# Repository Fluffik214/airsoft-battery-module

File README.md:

# Airsoft Battery Module

This is a USB-C PD charger and cell monitor for a **3S LiPo** that lives in an airsoft stock tube. It has one USB-C port. A PD charger charges the pack through it, and a phone plugged into the same port shows each cell's voltage and charge % in the companion Android app.

| | |
|---|---|
| Board | 135 × 21 mm, 2 layers, SMT only, no BGA |
| Pack | 3S LiPo (made for an iPower 1450 mAh stick). **Connects through the JST-XH balance plug only** (charging and cell sensing); the Deans lead goes straight to the gun |
| Charging | USB-C PD at 15 V (CH224K) → BQ25798 buck-boost charger |
| Monitoring | BQ7692003 (per-cell voltage, NTC, balancing) → STM32F042 → USB CDC |
| Idle drain | about 1 µA when unplugged |

## How it works

- **One port, two jobs.** On a PD charger the module charges. On a phone it only reports (5 V never charges, so the phone isn't drained). It never does both at once.
- **Charging rules:**
  - It starts after USB has stayed between 12 and 17 V for 5 s, then charges to your preset: Full, a custom %, Storage (3.80 V/cell) or Off.
  - If USB goes above 17 V, charging is cut immediately.
- **Per-cell control, like a hobby balance charger.** When a cell is full, it is held there and bled while the current is turned down, so the other cells can catch up. No cell goes more than 10 mV over the target.
- **JP2 solder jumper (back of the board).** Open (default) = slow charge, 700 mA. Bridged = fast charge, 1.4 A. Both currents can be changed in the app. Check your balance lead: on thin 26 AWG wires stay on slow charge.
- **Charging through the balance plug.** The charge current runs in the balance lead's outer wires (pins 1 and 4) through a 2.5 A fuse. The firmware pauses the charger for under a second every few seconds to read the cells without the wire voltage drop, so all three cells are measured accurately.
- **Cell LEDs.** Three wire pads (A, B, C) near the USB-C drive one red/green LED per cell on a small 20 × 10 mm LED board (`led_board/`) that sits on top of the stock tube: red = cell still charging, green = cell full. Solder A to A, B to B, C to C.
- **Event log in flash.** Faults (over-voltage, over-temperature, bad cell…) and a report for every charge are stored on the module. The app shows them the next time a phone is connected.

## Repository layout

| Path | Contents |
|---|---|
| `usbc pd airsoft module.kicad_*` | KiCad 10 project: schematic, routed PCB, design rules |
| `schematic.pdf`, `bom.csv` | Schematic printout and bill of materials |
| `DESIGN_NOTES.md` | Hardware notes: power path, pinouts, checks before first power-up |
| `layout_work/` | Python scripts that generated the schematic and placed/routed the PCB |
| `firmware/` | STM32F042 firmware: bare-metal C plus TinyUSB. **`firmware/README.md` is the full guide**, covering protocol, settings, safety rules and how to customize |
| `android/` | Android app: Kotlin, Jetpack Compose, Material 3 |
| `release/` | Prebuilt firmware (`.bin` / `.hex`) and app (`.apk`) |
| `production/` | Gerber zip for the board house, drill files, pick-and-place, BOM, assembly drawings, and `ORDERING.md` (fab settings). `production/led_board/` has the same set for the LED board |
| `led_board/` | KiCad project of the cell-LED board (schematic, routed PCB) plus its generator, checker and routing scripts |
| `3dmodels/` | 3D models KiCad doesn't ship: the J2 balance plug and the cell LED |

## Quick start

1. **Flash the firmware.** A blank chip starts in the USB DFU bootloader. You can also bridge JP1 while plugging in. Then:
   ```
   dfu-util -a 0 -s 0x08000000:leave -D release/airsoft_charger.bin
   ```
   STM32CubeProgrammer works too.
2. **Install the app.** Copy `release/PDCharger-1.0.0.apk` to the phone and install it.
3. **Check the pack.** Plug the module into the phone with a USB-C cable and open the app.
4. **Charge it.** Put the module on a USB-C PD charger that offers 15 V (or 12 V).

### Building from source

- **Firmware:** needs `arm-none-eabi-gcc` (tested with xPack 15.2.1). Run:
  ```
  python firmware/build.py --gcc <path-to-toolchain-bin>
  ```
- **App:** needs JDK 17 and the Android SDK. Run:
  ```
  cd android && ./gradlew assembleRelease
  ```

## Safety

LiPo batteries can catch fire. This is a hobby project with **no warranty**. Check `DESIGN_NOTES.md` before the first power-up. In particular, check your pack's balance plug against `production/assembly/J2-orientation.png`: J2 pin 4 is the pack's negative (black) wire.

## License

© Fluff. Licensed under **[Creative Commons Attribution-NonCommercial-ShareAlike 4.0](LICENSE)** (CC BY-NC-SA 4.0):

- You may copy, build and change this project for **non-commercial** use, if you credit the author and share your changes under the same license.
- **Commercial use, including selling boards, kits or devices built from this design, needs written permission from the author.**

Third-party code in `firmware/lib/` keeps its own license:

- **TinyUSB:** MIT, see `firmware/lib/tinyusb/LICENSE`.
- **ARM CMSIS core headers:** Apache-2.0 (SPDX header in each file).
- **ST device headers:** Apache-2.0, see `firmware/lib/cmsis/LICENSE-ST-cmsis-device-f0.md`.
- **J2 3D model** (`3dmodels/JST_XH_S4B-XH-SM4-TB.step`): from the JLCEDA/EasyEDA Official Library ([lceda.cn](https://lceda.cn/), [easyeda.com](https://easyeda.com)), see `3dmodels/README.md`.

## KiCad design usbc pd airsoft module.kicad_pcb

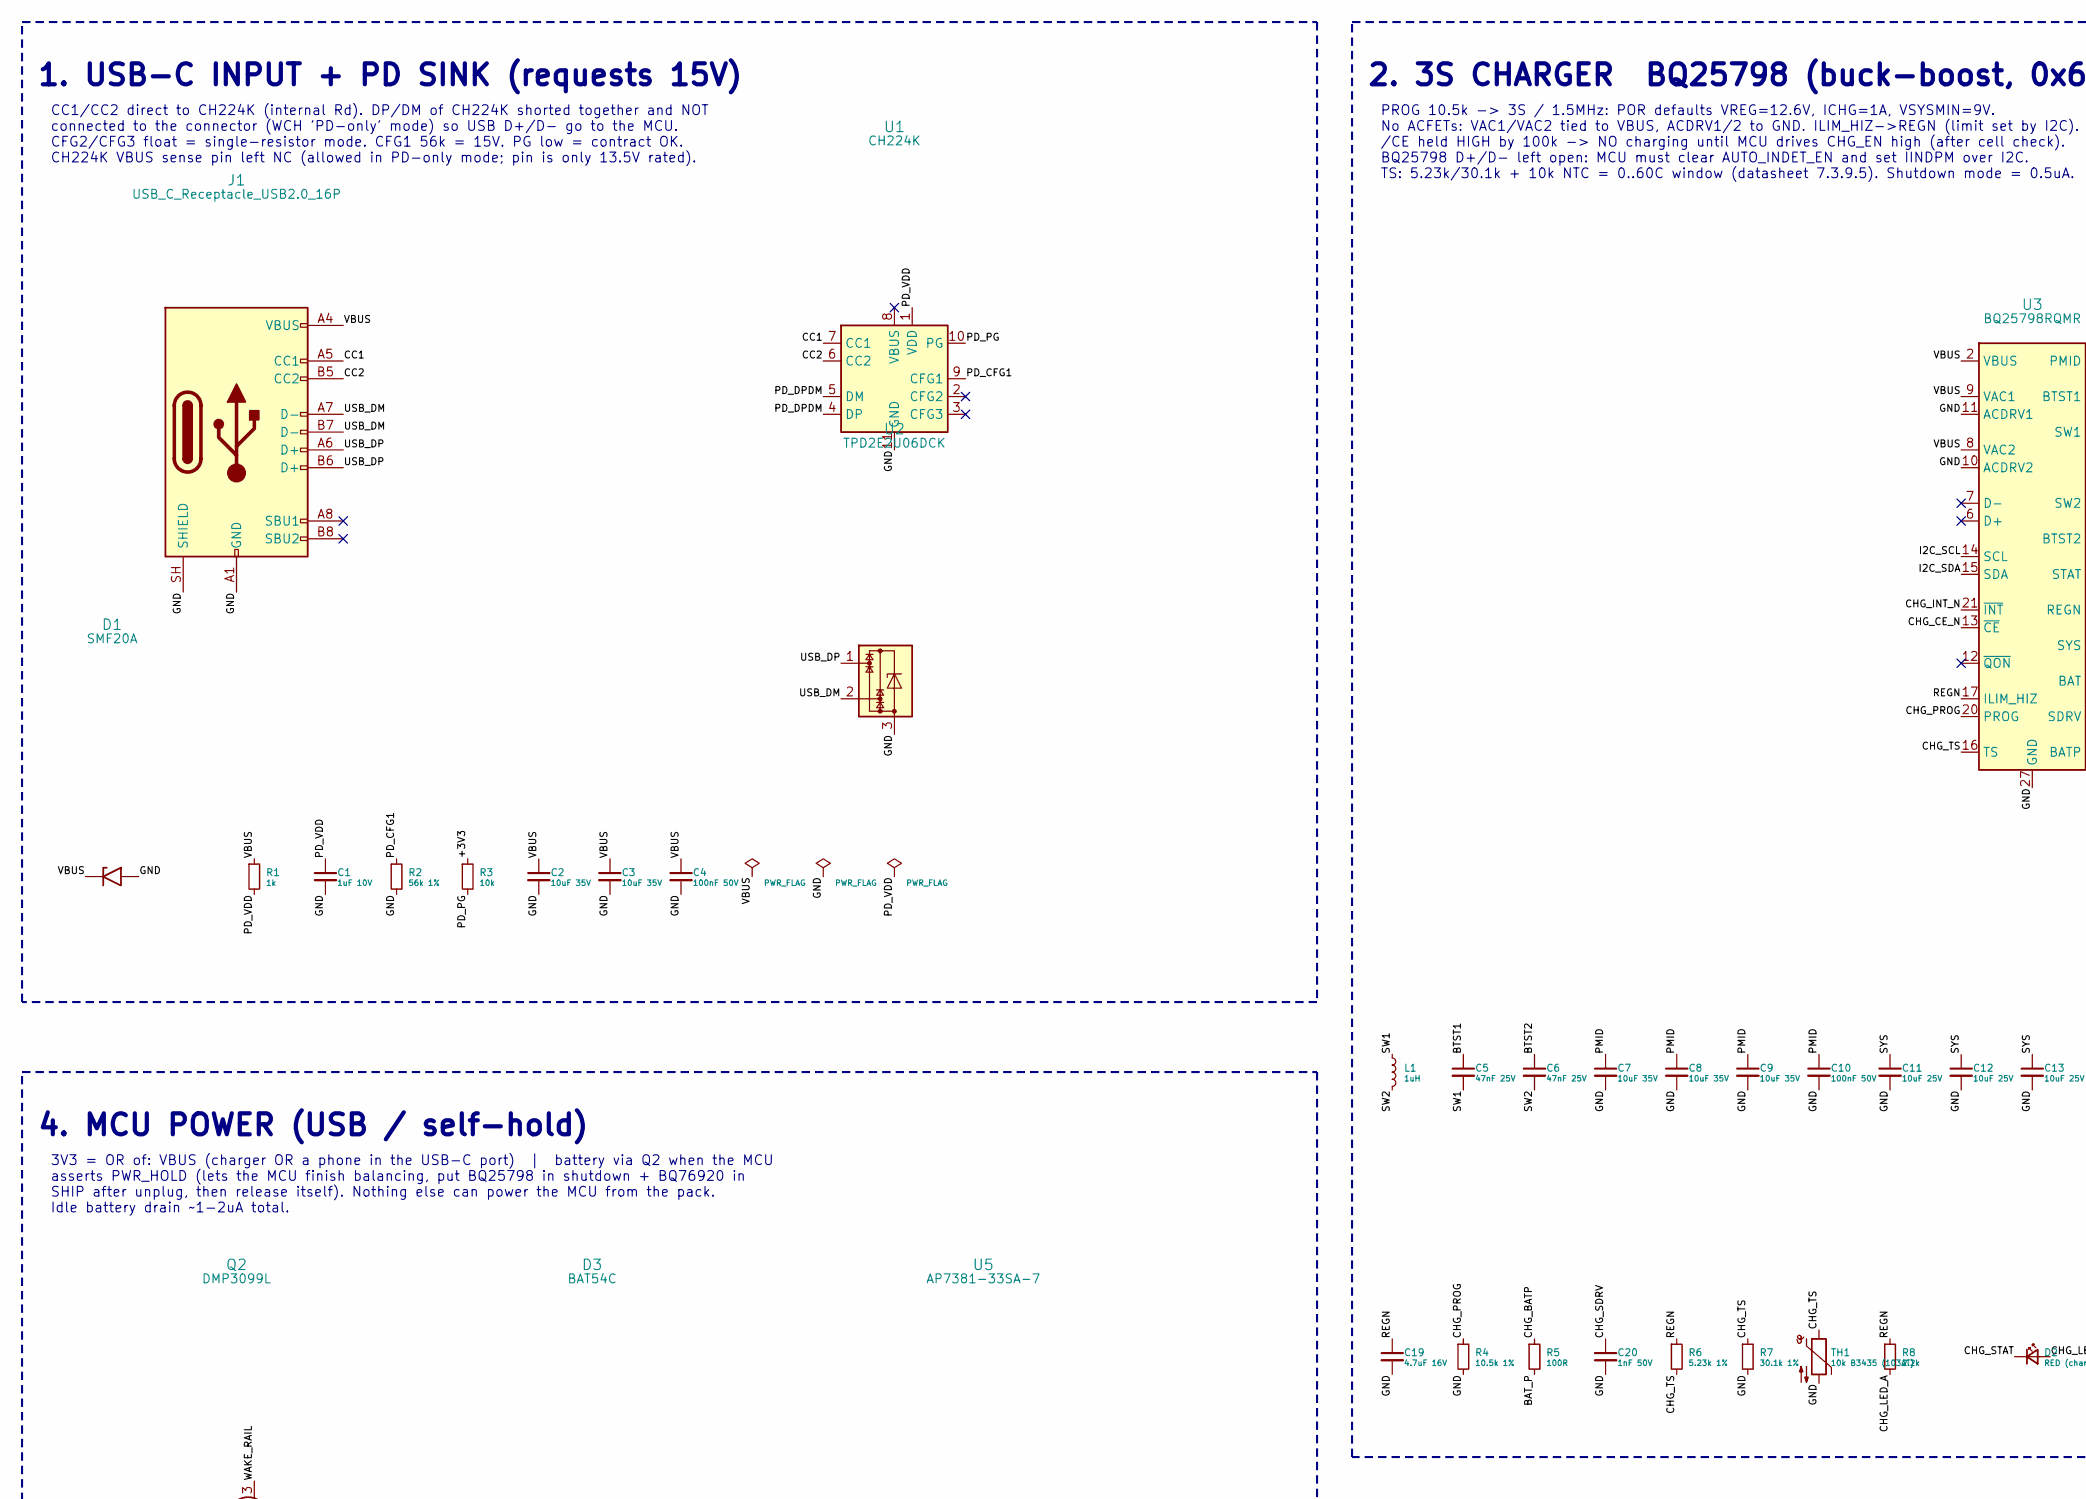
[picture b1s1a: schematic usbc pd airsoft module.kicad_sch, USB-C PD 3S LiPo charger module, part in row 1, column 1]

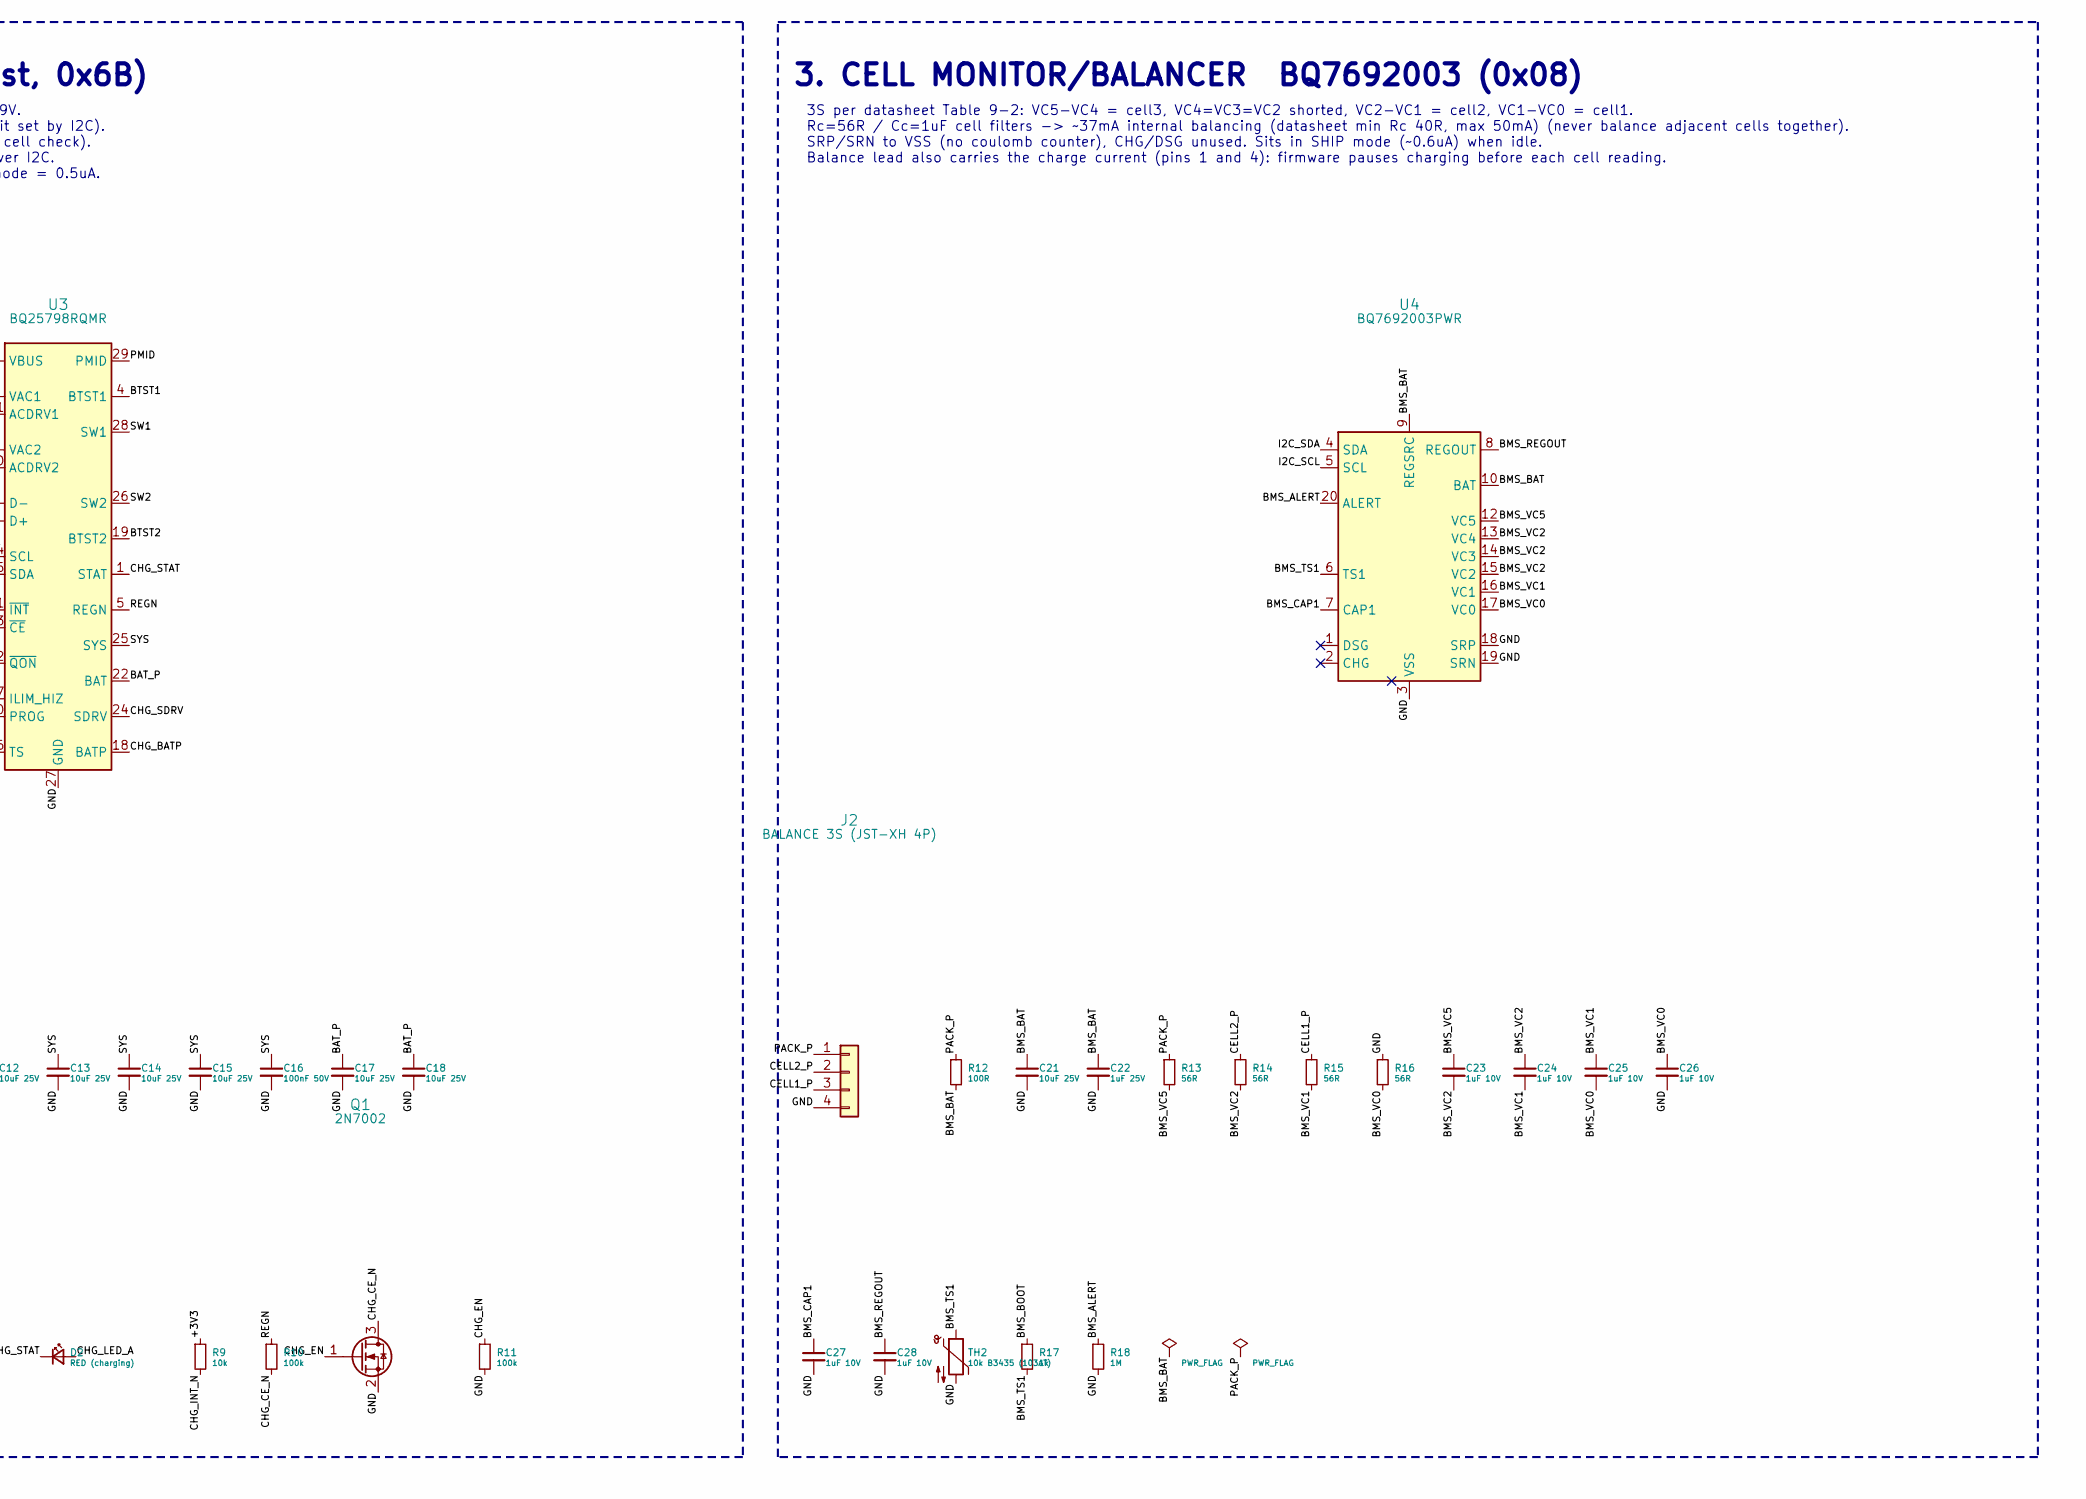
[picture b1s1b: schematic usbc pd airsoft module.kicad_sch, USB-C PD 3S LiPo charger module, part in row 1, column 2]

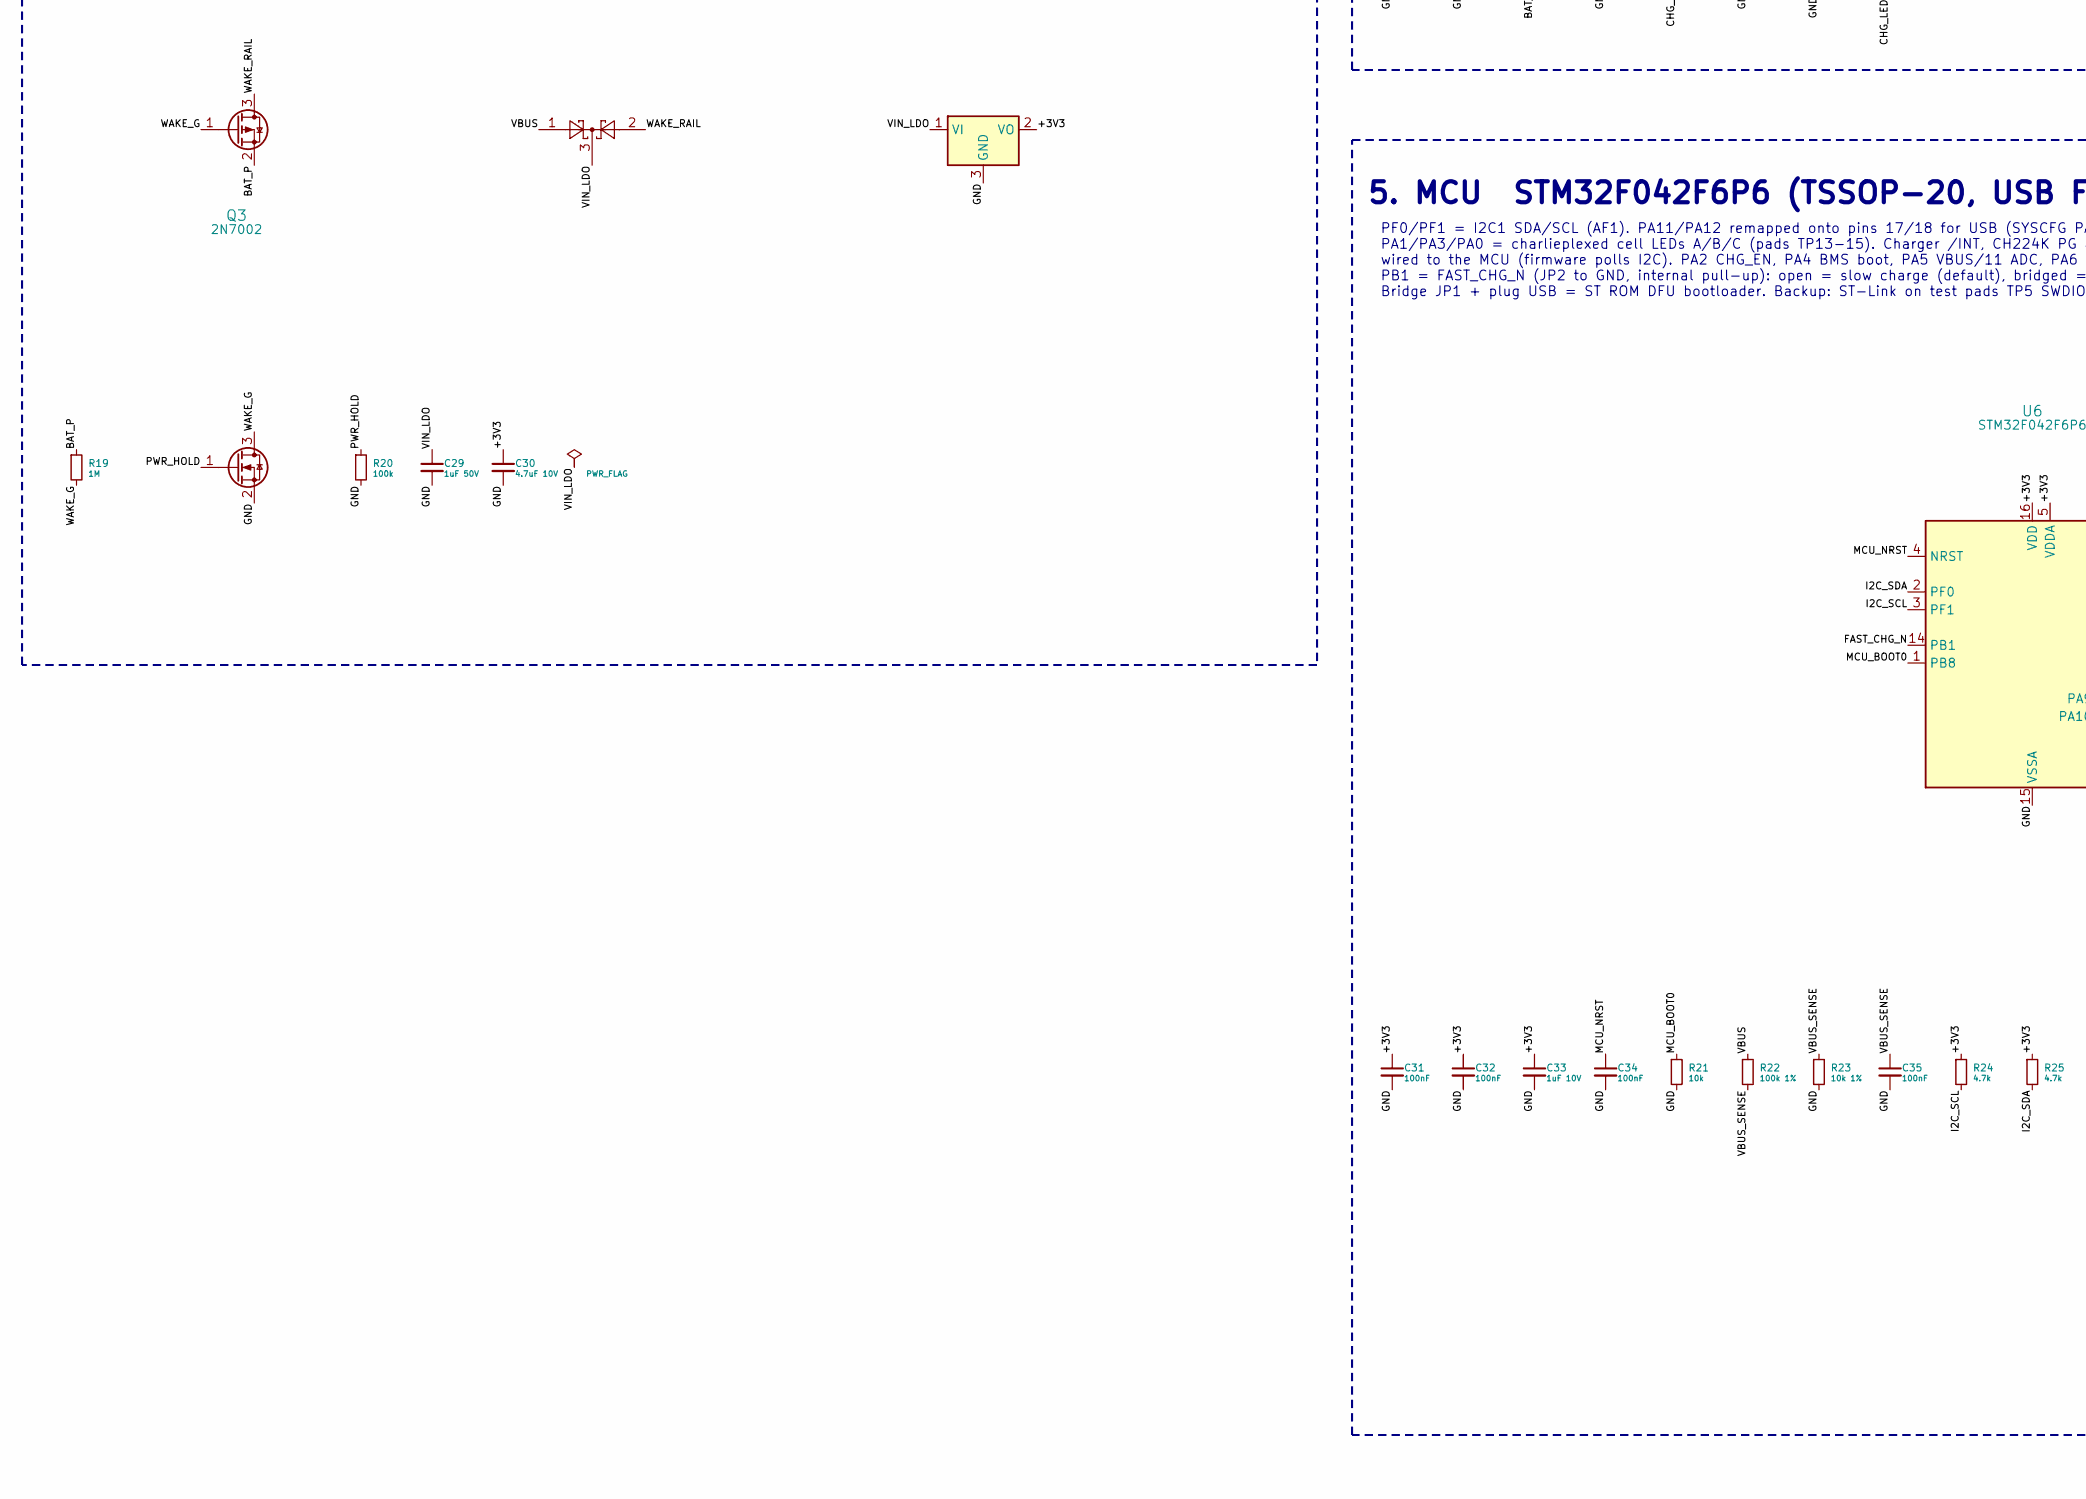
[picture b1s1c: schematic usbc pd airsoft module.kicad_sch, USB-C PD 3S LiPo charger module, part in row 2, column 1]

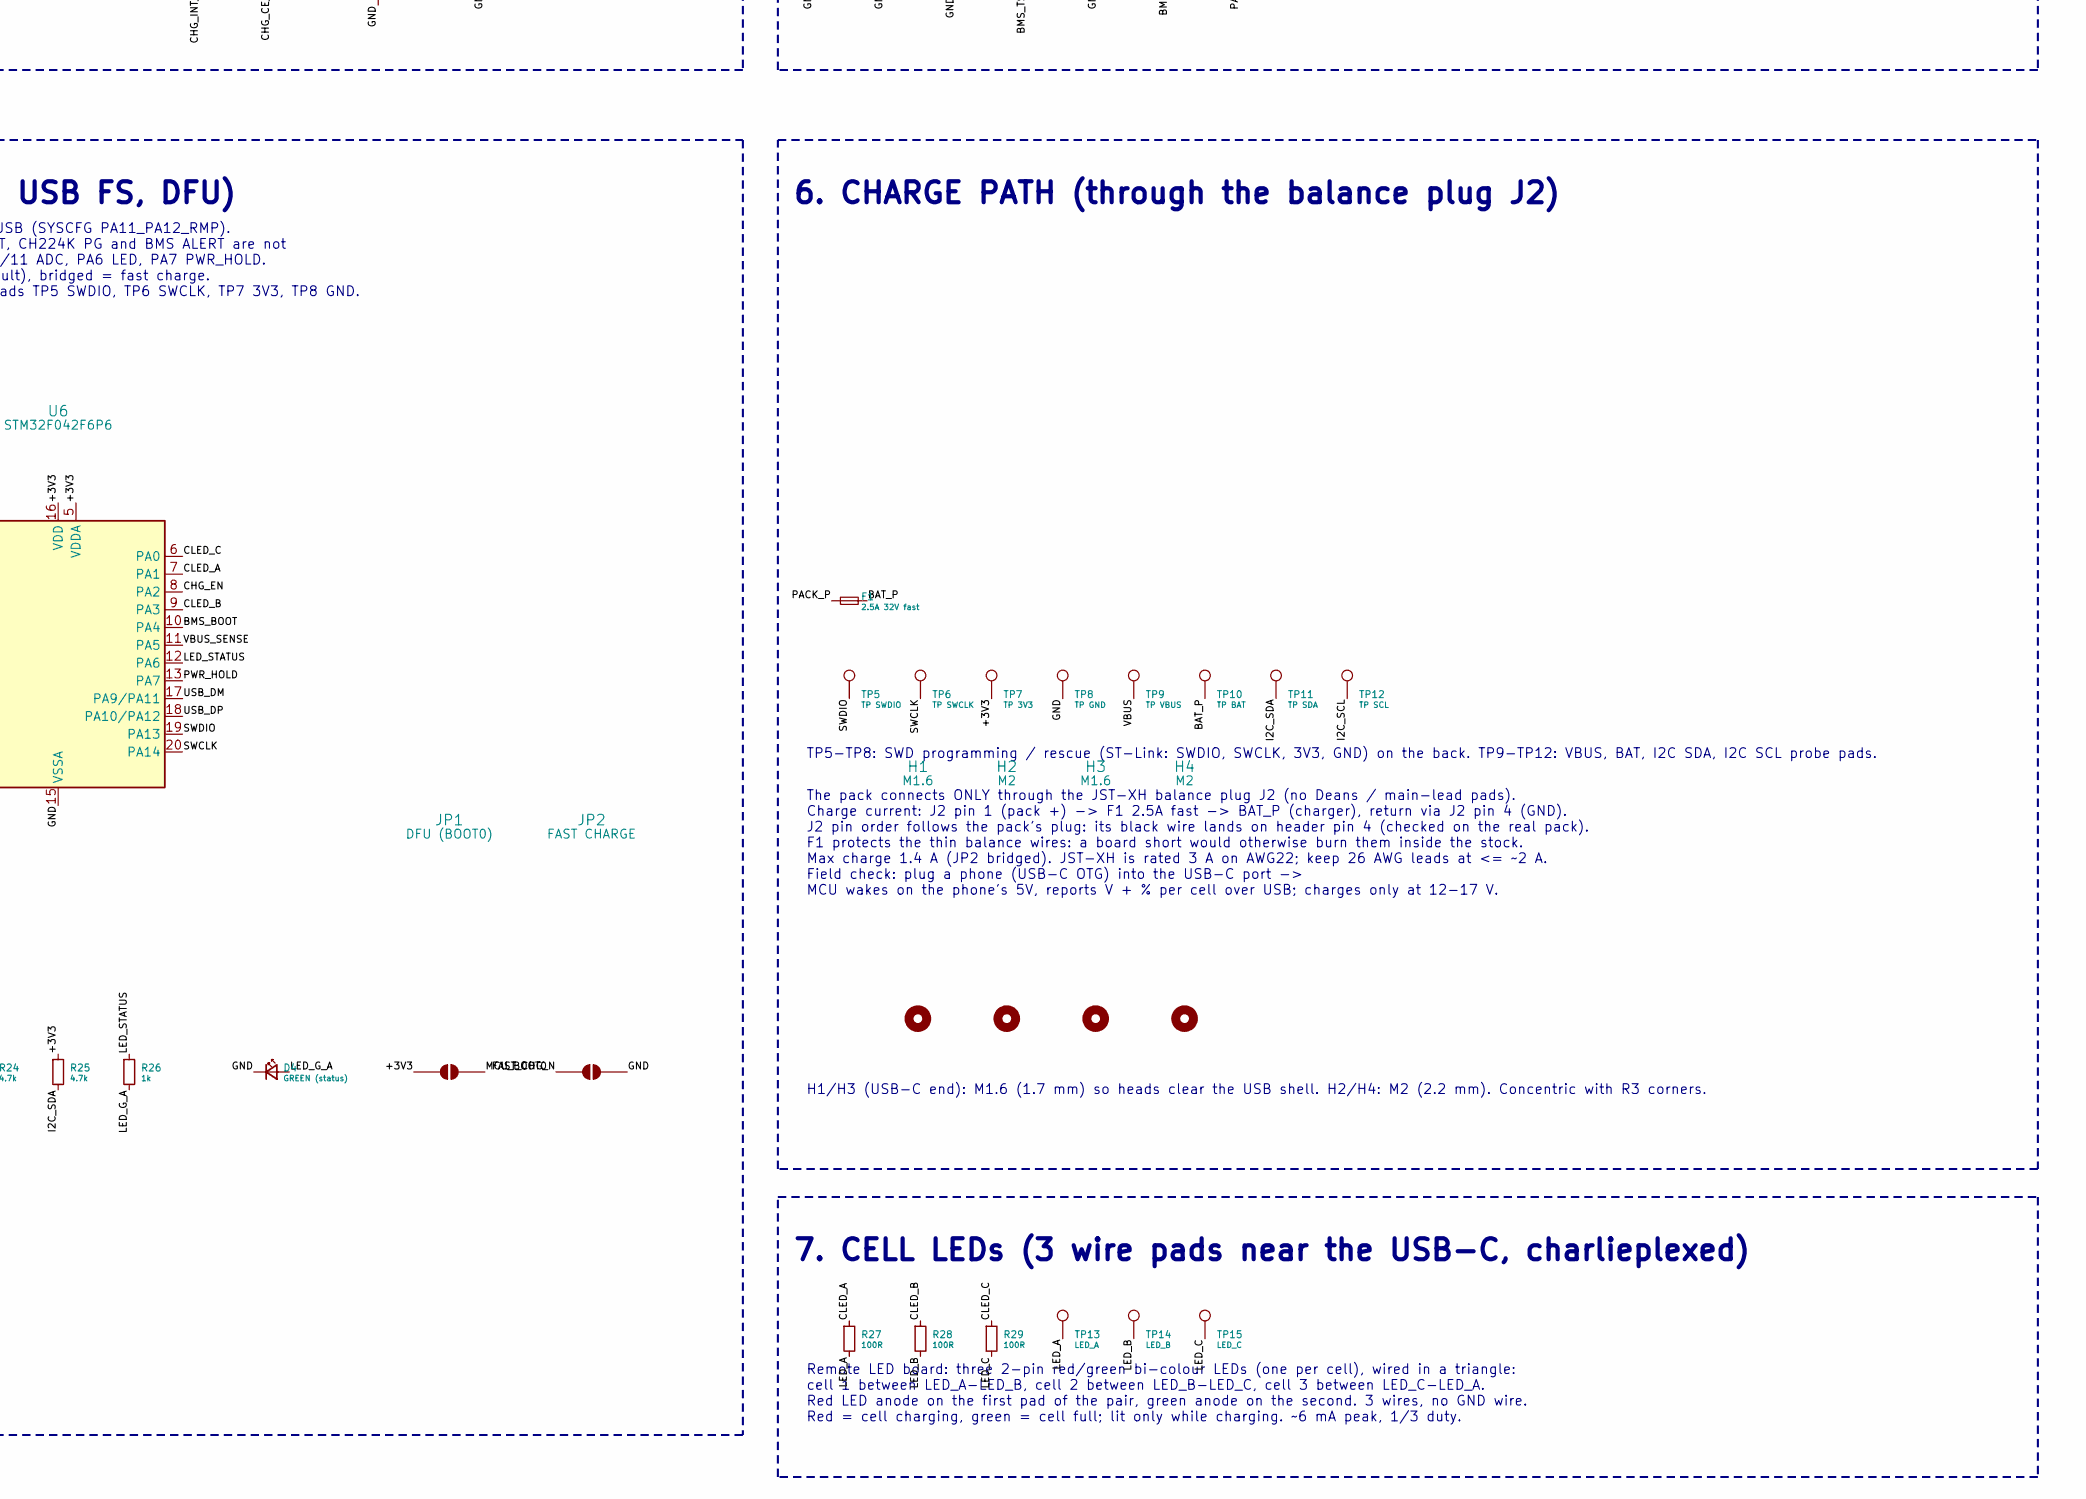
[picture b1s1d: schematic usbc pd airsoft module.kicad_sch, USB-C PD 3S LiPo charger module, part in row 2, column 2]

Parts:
C1, C23, C24, C25, C26, C27, C28, C33: 1uF 10V; C_0402_1005Metric
C2, C3, C7, C8, C9: 10uF 35V; C_0805_2012Metric
C4, C10, C16: 100nF 50V; C_0402_1005Metric
C5, C6: 47nF 25V; C_0402_1005Metric
C11, C12, C13, C14, C15, C17, C18, C21: 10uF 25V; C_0805_2012Metric
C19: 4.7uF 16V; C_0603_1608Metric
C20: 1nF 50V; C_0402_1005Metric
C22: 1uF 25V; C_0603_1608Metric
C29: 1uF 50V; C_0805_2012Metric
C30: 4.7uF 10V; C_0603_1608Metric
C31, C32, C34, C35: 100nF; C_0402_1005Metric
D1: SMF20A; D_SMF; MPN Littelfuse SMF20A (20V TVS)
D2: RED (charging); LED_0603_1608Metric
D3: BAT54C; SOT-23
D4: GREEN (status); LED_0603_1608Metric
F1: 2.5A 32V fast; Fuse_1206_3216Metric; MPN AEM F1206SB2500V032TM (LCSC C310999), 2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
H1, H3: M1.6; MountingHole_1.7mm_M1.6
H2, H4: M2; MountingHole_2.2mm_M2
J1: USB_C_Receptacle_USB2.0_16P; USB_C_Receptacle_HRO_TYPE-C-31-M-12; MPN HRO TYPE-C-31-M-12 (LCSC C165948)
J2: BALANCE 3S (JST-XH 4P); JST_XH_S4B-XH-SM4-TB_1x04-1MP_P2.50mm_Horizontal; MPN JST S4B-XH-SM4-TB
JP1: DFU (BOOT0); SolderJumper-2_P1.3mm_Open_RoundedPad1.0x1.5mm
JP2: FAST CHARGE; SolderJumper-2_P1.3mm_Open_RoundedPad1.0x1.5mm
L1: 1uH; L_Coilcraft_XAL4020-XXX; MPN Coilcraft XAL4020-102MEB
Q1, Q3: 2N7002; SOT-23
Q2: DMP3099L; SOT-23; MPN Diodes DMP3099L-7 (Vgs +-20V)
R1: 1k; R_1206_3216Metric
R2: 56k 1%; R_0402_1005Metric
R3, R9, R21: 10k; R_0402_1005Metric
R4: 10.5k 1%; R_0402_1005Metric
R5, R27, R28, R29: 100R; R_0402_1005Metric
R6: 5.23k 1%; R_0402_1005Metric
R7: 30.1k 1%; R_0402_1005Metric
R8: 2.2k; R_0402_1005Metric
R10, R11, R20: 100k; R_0402_1005Metric
R12: 100R; R_0603_1608Metric
R13, R14, R15, R16: 56R; R_0603_1608Metric
R17, R26: 1k; R_0402_1005Metric
R18, R19: 1M; R_0402_1005Metric
R22: 100k 1%; R_0402_1005Metric
R23: 10k 1%; R_0402_1005Metric
R24, R25: 4.7k; R_0402_1005Metric
TH1, TH2: 10k B3435 (103AT); R_0402_1005Metric; MPN Murata NCP15XH103F03RC
TP5: TP SWDIO; TestPoint_Pad_D1.0mm
TP6: TP SWCLK; TestPoint_Pad_D1.0mm
TP7: TP 3V3; TestPoint_Pad_D1.0mm
TP8: TP GND; TestPoint_Pad_D1.0mm
TP9: TP VBUS; TestPoint_Pad_D1.0mm
TP10: TP BAT; TestPoint_Pad_D1.0mm
TP11: TP SDA; TestPoint_Pad_D1.0mm
TP12: TP SCL; TestPoint_Pad_D1.0mm
TP13: LED_A; TestPoint_Pad_D1.5mm
TP14: LED_B; TestPoint_Pad_D1.5mm
TP15: LED_C; TestPoint_Pad_D1.5mm
U1: CH224K; SSOP-10-1EP_3.9x4.9mm_P1mm_EP2.1x3.3mm; MPN WCH CH224K (LCSC C970725)
U2: TPD2E2U06DCK; SOT-323_SC-70; MPN TI TPD2E2U06DCKR
U3: BQ25798RQMR; Texas_RQM0029A_VQFN-29_4x4mm_P0.4mm; MPN TI BQ25798RQMR
U4: BQ7692003PWR; TSSOP-20_4.4x6.5mm_P0.65mm; MPN TI BQ7692003PWR (3.3V LDO, addr 0x08, C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
U5: AP7381-33SA-7; SOT-23; MPN Diodes AP7381-33SA-7 (40V in)
U6: STM32F042F6P6; TSSOP-20_4.4x6.5mm_P0.65mm; MPN ST STM32F042F6P6

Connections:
/+3V3: C30.1, C31.1, C32.1, C33.1, JP1.1 (A), R3.1, R9.1, R24.1, R25.1, TP7.1, U5.2 (VO), U6.5 (VDDA), U6.16 (VDD)
/BAT_P: C17.1, C18.1, F1.2, Q2.2 (S), R5.2, R19.1, TP10.1, U3.22 (BAT), U3.23 (BAT)
/BMS_ALERT: R18.1, U4.20 (ALERT)
/BMS_BAT: C21.1, C22.1, R12.2, U4.9 (REGSRC), U4.10 (BAT)
/BMS_BOOT: R17.1, U6.10 (PA4)
/BMS_CAP1: C27.1, U4.7 (CAP1)
/BMS_REGOUT: C28.1, U4.8 (REGOUT)
/BMS_TS1: R17.2, TH2.1, U4.6 (TS1)
/BMS_VC0: C25.2, C26.1, R16.2, U4.17 (VC0)
/BMS_VC1: C24.2, C25.1, R15.2, U4.16 (VC1)
/BMS_VC2: C23.2, C24.1, R14.2, U4.13 (VC4), U4.14 (VC3), U4.15 (VC2)
/BMS_VC5: C23.1, R13.2, U4.12 (VC5)
/BTST1: C5.1, U3.4 (BTST1)
/BTST2: C6.1, U3.19 (BTST2)
/CC1: J1.A5 (CC1), U1.7 (CC1)
/CC2: J1.B5 (CC2), U1.6 (CC2)
/CELL1_P: J2.3, R15.1
/CELL2_P: J2.2, R14.1
/CHG_BATP: R5.1, U3.18 (BATP)
/CHG_CE_N: Q1.3 (D), R10.2, U3.13 (~CE)
/CHG_EN: Q1.1 (G), R11.1, U6.8 (PA2)
/CHG_INT_N: R9.2, U3.21 (~INT)
/CHG_LED_A: D2.2 (A), R8.2
/CHG_PROG: R4.1, U3.20 (PROG)
/CHG_SDRV: C20.1, U3.24 (SDRV)
/CHG_STAT: D2.1 (K), U3.1 (STAT)
/CHG_TS: R6.2, R7.1, TH1.1, U3.16 (TS)
/CLED_A: R27.1, U6.7 (PA1)
/CLED_B: R28.1, U6.9 (PA3)
/CLED_C: R29.1, U6.6 (PA0)
/FAST_CHG_N: JP2.1 (A), U6.14 (PB1)
/GND: C1.2, C2.2, C3.2, C4.2, C7.2, C8.2, C9.2, C10.2, C11.2, C12.2, C13.2, C14.2, C15.2, C16.2, C17.2, C18.2, C19.2, C20.2, C21.2, C22.2, C26.2, C27.2, C28.2, C29.2, C30.2, C31.2, C32.2, C33.2, C34.2, C35.2, D1.2 (A2), D4.1 (K), J1.A1 (GND), J1.A12 (GND), J1.B1 (GND), J1.B12 (GND), J1.SH (SHIELD), J2.4, JP2.2 (B), Q1.2 (S), Q3.2 (S), R2.2, R4.2, R7.2, R11.2, R16.1, R18.2, R20.2, R21.2, R23.2, TH1.2, TH2.2, TP8.1, U1.11 (GND), U2.3, U3.10 (ACDRV2), U3.11 (ACDRV1), U3.27 (GND), U4.3 (VSS), U4.18 (SRP), U4.19 (SRN), U5.3 (GND), U6.15 (VSSA)
/I2C_SCL: R24.2, TP12.1, U3.14 (SCL), U4.5 (SCL), U6.3 (PF1)
/I2C_SDA: R25.2, TP11.1, U3.15 (SDA), U4.4 (SDA), U6.2 (PF0)
/LED_A: R27.2, TP13.1
/LED_B: R28.2, TP14.1
/LED_C: R29.2, TP15.1
/LED_G_A: D4.2 (A), R26.2
/LED_STATUS: R26.1, U6.12 (PA6)
/MCU_BOOT0: JP1.2 (B), R21.1, U6.1 (PB8)
/MCU_NRST: C34.1, U6.4 (NRST)
/PACK_P: F1.1, J2.1, R12.1, R13.1
/PD_CFG1: R2.1, U1.9 (CFG1)
/PD_DPDM: U1.4 (DP), U1.5 (DM)
/PD_PG: R3.2, U1.10 (PG)
/PD_VDD: C1.1, R1.2, U1.1 (VDD)
/PMID: C7.1, C8.1, C9.1, C10.1, U3.29 (PMID)
/PWR_HOLD: Q3.1 (G), R20.1, U6.13 (PA7)
/REGN: C19.1, R6.1, R8.1, R10.1, U3.5 (REGN), U3.17 (ILIM_HIZ)
/SW1: C5.2, L1.1, U3.28 (SW1)
/SW2: C6.2, L1.2, U3.26 (SW2)
/SWCLK: TP6.1, U6.20 (PA14)
/SWDIO: TP5.1, U6.19 (PA13)
/SYS: C11.1, C12.1, C13.1, C14.1, C15.1, C16.1, U3.25 (SYS)
/USB_DM: J1.A7 (D-), J1.B7 (D-), U2.2, U6.17 (PA9/PA11)
/USB_DP: J1.A6 (D+), J1.B6 (D+), U2.1, U6.18 (PA10/PA12)
/VBUS: C2.1, C3.1, C4.1, D1.1 (A1), D3.1, J1.A4 (VBUS), J1.A9 (VBUS), J1.B4 (VBUS), J1.B9 (VBUS), R1.1, R22.1, TP9.1, U3.2 (VBUS), U3.3 (VBUS), U3.8 (VAC2), U3.9 (VAC1)
/VBUS_SENSE: C35.1, R22.2, R23.1, U6.11 (PA5)
/VIN_LDO: C29.1, D3.3, U5.1 (VI)
/WAKE_G: Q2.1 (G), Q3.3 (D), R19.2
/WAKE_RAIL: D3.2, Q2.3 (D)

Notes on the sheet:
1. USB-C INPUT + PD SINK (requests 15V)
CC1/CC2 direct to CH224K (internal Rd). DP/DM of CH224K shorted together and NOT connected to the connector (WCH 'PD-only' mode) so USB D+/D- go to the MCU. CFG2/CFG3 float = single-resistor mode. CFG1 56k = 15V. PG low = contract OK. CH224K VBUS sense pin left NC (allowed in PD-only mode; pin is o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
2. 3S CHARGER BQ25798 (buck-boost, 0x6B)
PROG 10.5k -> 3S / 1.5MHz: POR defaults VREG=12.6V, ICHG=1A, VSYSMIN=9V. No ACFETs: VAC1/VAC2 tied to VBUS, ACDRV1/2 to GND. ILIM_HIZ->REGN (limit set by I2C). /CE held HIGH by 100k -> NO charging until MCU drives CHG_EN high (after cell check). BQ25798 D+/D- left open: MCU must clear AUTO_INDET_EN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
3. CELL MONITOR/BALANCER BQ7692003 (0x08)
3S per datasheet Table 9-2: VC5-VC4 = cell3, VC4=VC3=VC2 shorted, VC2-VC1 = cell2, VC1-VC0 = cell1. Rc=56R / Cc=1uF cell filters -> ~37mA internal balancing (datasheet min Rc 40R, max 50mA) (never balance adjacent cells together). SRP/SRN to VSS (no coulomb counter), CHG/DSG unused. Sits in SHIP mo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
4. MCU POWER (USB / self-hold)
3V3 = OR of: VBUS (charger OR a phone in the USB-C port) | battery via Q2 when the MCU asserts PWR_HOLD (lets the MCU finish balancing, put BQ25798 in shutdown + BQ76920 in SHIP after unplug, then release itself). Nothing else can power the MCU from the pack. Idle battery drain ~1-2uA total.
5. MCU STM32F042F6P6 (TSSOP-20, USB FS, DFU)
PF0/PF1 = I2C1 SDA/SCL (AF1). PA11/PA12 remapped onto pins 17/18 for USB (SYSCFG PA11_PA12_RMP). PA1/PA3/PA0 = charlieplexed cell LEDs A/B/C (pads TP13-15). Charger /INT, CH224K PG and BMS ALERT are not wired to the MCU (firmware polls I2C). PA2 CHG_EN, PA4 BMS boot, PA5 VBUS/11 ADC, PA6 LED, PA7 P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
6. CHARGE PATH (through the balance plug J2)
The pack connects ONLY through the JST-XH balance plug J2 (no Deans / main-lead pads). Charge current: J2 pin 1 (pack +) -> F1 2.5A fast -> BAT_P (charger), return via J2 pin 4 (GND). J2 pin order follows the pack's plug: its black wire lands on header pin 4 (checked on the real pack). F1 protects 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
H1/H3 (USB-C end): M1.6 (1.7 mm) so heads clear the USB shell. H2/H4: M2 (2.2 mm). Concentric with R3 corners.
TP5-TP8: SWD programming / rescue (ST-Link: SWDIO, SWCLK, 3V3, GND) on the back. TP9-TP12: VBUS, BAT, I2C SDA, I2C SCL probe pads.
7. CELL LEDs (3 wire pads near the USB-C, charlieplexed)
Remote LED board: three 2-pin red/green bi-colour LEDs (one per cell), wired in a triangle: cell 1 between LED_A-LED_B, cell 2 between LED_B-LED_C, cell 3 between LED_C-LED_A. Red LED anode on the first pad of the pair, green anode on the second. 3 wires, no GND wire. Red = cell charging, green = c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

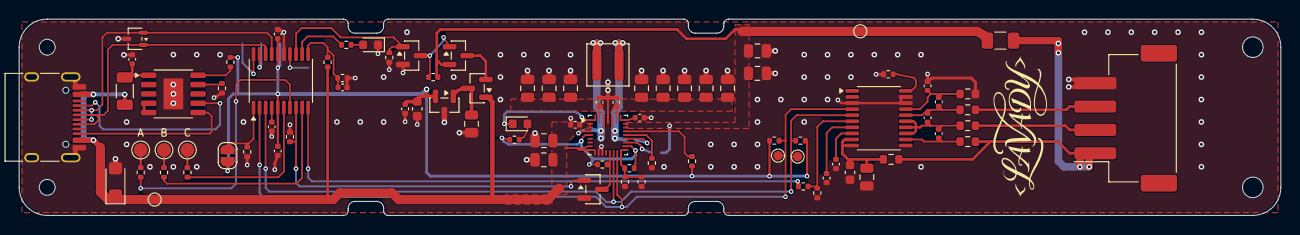
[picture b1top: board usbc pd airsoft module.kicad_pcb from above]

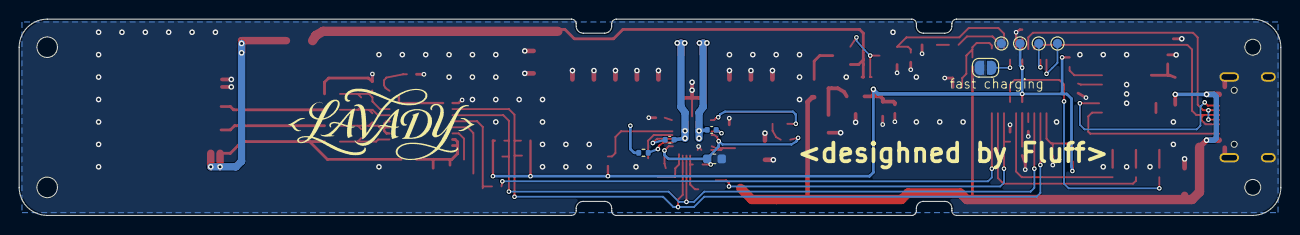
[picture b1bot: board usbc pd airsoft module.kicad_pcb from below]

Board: 2 copper layers, 135.0 x 21.0 mm, 102 parts (10 on the bottom side), 61 nets.

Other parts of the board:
LOGO*: LOGO; LAVADY logo 15x5.7mm
LOGO*#2: LOGO; LAVADY logo 20x7.7mm

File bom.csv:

"Refs","Value","Footprint","MPN","Note","Qty"
"C1,C23-C28,C33","1uF 10V","Capacitor_SMD:C_0402_1005Metric","","","8"
"C2,C3,C7-C9","10uF 35V","Capacitor_SMD:C_0805_2012Metric","","","5"
"C4,C10,C16","100nF 50V","Capacitor_SMD:C_0402_1005Metric","","","3"
"C5,C6","47nF 25V","Capacitor_SMD:C_0402_1005Metric","","","2"
"C11-C15,C17,C18,C21","10uF 25V","Capacitor_SMD:C_0805_2012Metric","","Cf supply filter","8"
"C19","4.7uF 16V","Capacitor_SMD:C_0603_1608Metric","","","1"
"C20","1nF 50V","Capacitor_SMD:C_0402_1005Metric","","no ship FET fitted","1"
"C22","1uF 25V","Capacitor_SMD:C_0603_1608Metric","","REGSRC cap","1"
"C29","1uF 50V","Capacitor_SMD:C_0805_2012Metric","","","1"
"C30","4.7uF 10V","Capacitor_SMD:C_0603_1608Metric","","","1"
"C31,C32,C34,C35","100nF","Capacitor_SMD:C_0402_1005Metric","","","4"
"D1","SMF20A","Diode_SMD:D_SMF","Littelfuse SMF20A (20V TVS)","","1"
"D2","RED (charging)","LED_SMD:LED_0603_1608Metric","","","1"
"D3","BAT54C","Package_TO_SOT_SMD:SOT-23","","","1"
"D4","GREEN (status)","LED_SMD:LED_0603_1608Metric","","","1"
"F1","2.5A 32V fast","Fuse:Fuse_1206_3216Metric","AEM F1206SB2500V032TM (LCSC C310999), 2.5A fast, 50A breaking","protects the balance-lead wires (charge path J2 pin 1)","1"
"J1","USB_C_Receptacle_USB2.0_16P","Connector_USB:USB_C_Receptacle_HRO_TYPE-C-31-M-12","HRO TYPE-C-31-M-12 (LCSC C165948)","","1"
"J2","BALANCE 3S (JST-XH 4P)","Connector_JST:JST_XH_S4B-XH-SM4-TB_1x04-1MP_P2.50mm_Horizontal","JST S4B-XH-SM4-TB","Pin4 = pack NEGATIVE (black), pin1 = pack + (red): set by the pack plug","1"
"L1","1uH","Inductor_SMD:L_Coilcraft_XAL4020-XXX","Coilcraft XAL4020-102MEB","","1"
"Q1,Q3","2N7002","Package_TO_SOT_SMD:SOT-23","","","2"
"Q2","DMP3099L","Package_TO_SOT_SMD:SOT-23","Diodes DMP3099L-7 (Vgs +-20V)","","1"
"R1","1k","Resistor_SMD:R_1206_3216Metric","","CH224K VDD shunt feed, 1/4W","1"
"R2","56k 1%","Resistor_SMD:R_0402_1005Metric","","56k on CFG1 = request 15V","1"
"R3,R9,R21","10k","Resistor_SMD:R_0402_1005Metric","","","3"
"R4","10.5k 1%","Resistor_SMD:R_0402_1005Metric","","PROG: 3S, 1.5MHz","1"
"R5,R27-R29","100R","Resistor_SMD:R_0402_1005Metric","","R27-R29 = cell LED lines (charlieplexed)","4"
"R6","5.23k 1%","Resistor_SMD:R_0402_1005Metric","","","1"
"R7","30.1k 1%","Resistor_SMD:R_0402_1005Metric","","","1"
"R8","2.2k","Resistor_SMD:R_0402_1005Metric","","","1"
"R10,R11,R20","100k","Resistor_SMD:R_0402_1005Metric","","charging disabled by default","3"
"R12","100R","Resistor_SMD:R_0603_1608Metric","","Rf supply filter","1"
"R13-R16","56R","Resistor_SMD:R_0603_1608Metric","","Cell input Rc (sets ~37 mA balance current), 1%, >=0.1 W","4"
"R17,R26","1k","Resistor_SMD:R_0402_1005Metric","","MCU pulses BMS_BOOT high 5ms to wake from SHIP","2"
"R18,R19","1M","Resistor_SMD:R_0402_1005Metric","","","2"
"R22","100k 1%","Resistor_SMD:R_0402_1005Metric","","","1"
"R23","10k 1%","Resistor_SMD:R_0402_1005Metric","","","1"
"R24,R25","4.7k","Resistor_SMD:R_0402_1005Metric","","","2"
"TH1,TH2","10k B3435 (103AT)","Resistor_SMD:R_0402_1005Metric","Murata NCP15XH103F03RC","Place at board edge touching the pack","2"
"U1","CH224K","Package_SO:SSOP-10-1EP_3.9x4.9mm_P1mm_EP2.1x3.3mm","WCH CH224K (LCSC C970725)","","1"
"U2","TPD2E2U06DCK","Package_TO_SOT_SMD:SOT-323_SC-70","TI TPD2E2U06DCKR","","1"
"U3","BQ25798RQMR","Package_DFN_QFN:Texas_RQM0029A_VQFN-29_4x4mm_P0.4mm","TI BQ25798RQMR","","1"
"U4","BQ7692003PWR","Package_SO:TSSOP-20_4.4x6.5mm_P0.65mm","TI BQ7692003PWR (3.3V LDO, addr 0x08, CRC)","","1"
"U5","AP7381-33SA-7","Package_TO_SOT_SMD:SOT-23","Diodes AP7381-33SA-7 (40V in)","","1"
"U6","STM32F042F6P6","Package_SO:TSSOP-20_4.4x6.5mm_P0.65mm","ST STM32F042F6P6","","1"
